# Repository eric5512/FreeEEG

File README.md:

# FreeEEG

FreeEEG is a low-cost, open-source electroencephalography (EEG) acquisition platform designed for educational, experimental, and research-oriented applications. The project aims to provide an accessible and modifiable EEG system for researchers, students, and hobbyists who need direct control over the acquisition hardware, firmware, and data interface.

The platform is based on the **Texas Instruments ADS1299** analog front-end and an **ESP32-S3** microcontroller. It supports multichannel EEG acquisition, real-time wireless data transmission, onboard storage, and motion sensing through an integrated IMU.

> **Safety notice:** FreeEEG is not a medical device. It has not been medically certified and must not be used for clinical diagnosis, treatment, or any safety-critical medical application.

## Project Overview

The system was developed as a Master Thesis project at the Institut d'Investigacions Biomèdiques August Pi i Sunyer (IDIBAPS). The main objective is to create an open-source and open-hardware EEG platform that is cost-effective, configurable, and easy to adapt to different experimental scenarios.

The current prototype integrates:

- 8-channel EEG acquisition
- ADS1299 24-bit analog front-end
- ESP32-S3 microcontroller
- WiFi access point mode
- UDP real-time data streaming
- HTTP-based configuration interface
- SD card storage through SDIO
- ICM42670 accelerometer and gyroscope
- ICS43434 microphone
- QWIIC connector for I2C external peripherals
- Battery-powered operation
- Python client library for receiving and decoding data

## Repository Structure

```text
FreeEEG/
├── Client/
│   └── Python library and tools for interacting with the device
│
├── Electronics/
│   └── KiCad schematic, PCB layout, and manufacturing files
│
├── Firmware/
│   └── ESP32-S3 firmware based on ESP-IDF and FreeRTOS
│
└── README.md
```

## Hardware Architecture

The hardware is centered around the ADS1299, an 8-channel, 24-bit analog front-end designed for EEG and biopotential measurements. The ESP32-S3 handles acquisition control, wireless communication, SD card storage, configuration, and system management.

Main hardware components:

| Subsystem | Component |
|---|---|
| Analog front-end | ADS1299 |
| Microcontroller | ESP32-S3 |
| IMU | ICM42670 |
| Microphone | ICS43434 |
| Storage | microSD card |
| Wireless communication | ESP32-S3 WiFi |
| Configuration interface | HTTP server |
| Real-time streaming | UDP |
| PCB design tool | KiCad |

> **Warning:** The PCB still presents some issues in its current form. More modifications need to be introduced to release the first fully functional version

## Firmware

The firmware is developed using **ESP-IDF** and **FreeRTOS**. It is organized into concurrent tasks to separate time-critical acquisition from communication, storage, and configuration logic.

Main firmware functions:

- ADS1299 initialization and register configuration
- EEG acquisition synchronized with the ADS1299 `DRDY` signal
- IMU acquisition over I2C
- UDP packet transmission in online mode
- CSV data logging to SD card in offline mode
- HTTP configuration server
- Mode selection through a physical switch

The firmware supports two operating modes:

### Online Mode

In online mode, the ESP32-S3 creates a WiFi access point and waits for UDP commands from the client. EEG and IMU data are transmitted in real time using UDP packets.

### Offline Mode

In offline mode, acquisition starts automatically and data are stored locally on the SD card in CSV format. WiFi is disabled to reduce power consumption.

## Client Library

The `Client/` folder contains the Python interface used to communicate with the device. The client library provides a higher-level interface for:

- Connecting to the FreeEEG device
- Sending start and stop commands
- Receiving UDP data packets
- Decoding EEG, IMU, and event data
- Exporting samples to CSV
- Building custom visualization or processing tools

Basic usage example:

```python
from freeeeg import FreeEEG
import signal

if __name__ == "__main__":
    eeg = FreeEEG()

    def signal_handler(sig, frame):
        f.close()
        eeg.stop()
        print("Stopping measurements")
        exit(0)

    signal.signal(signal.SIGINT, signal_handler)

    data_stream = eeg.get_data_generator(blocking=True)

    f = open("test.csv", "w+")
    eeg.start()

    print("Starting EEG...")
    f.write("timestamp,e1,e2,e3,e4,e5,e6,e7,e8,ax,ay,az,gx,gy,gz,event\n")

    for sample in data_stream():
        f.write(sample.as_csv() + "\n")
```

## Electronics

The `Electronics/` folder contains the KiCad project files needed to inspect, modify, and manufacture the PCB.

This folder may include:

- KiCad schematic files
- KiCad PCB layout files
- Symbol and footprint libraries
- Gerber files
- Drill files
- Bill of materials
- Assembly files

The current PCB revision is an engineering prototype. Before manufacturing or using the board, review the schematic, layout, footprints, and known issues.

## Current Prototype Status

The current version should be considered a functional engineering prototype. Several subsystems have been validated, including ADS1299 communication, EEG acquisition using the evaluation platform, WiFi access point creation, UDP transmission, HTTP configuration, and Python packet decoding.

Preliminary validation demonstrated:

- EEG acquisition with dry electrodes
- Resting-state EEG activity with a visible alpha-band peak around 10 Hz
- Shorted-input RMS noise around 0.2 µV RMS
- Stable UDP transmission at approximately 100 packets/s
- Packet loss at higher packet rates around 250 packets/s
- Approximate current consumption of 110 mA in online mode and 60 mA in offline mode
- Indoor wireless range around 10 m

## Known Limitations

The current prototype has several limitations:

- Not medically certified
- Not intended for clinical or diagnostic use
- Firmware validation still ongoing
- No integrated electrode impedance measurement
- No dedicated external synchronization connector in the current revision
- Long-duration validation is still required

## Planned Improvements

Future development may include:

- Complete firmware validation
- Full integration testing
- Electrode impedance measurement
- Improved analog filtering
- Bluetooth or mobile interface support
- Real-time visualization tools
- Signal processing and neurofeedback utilities

## Development Requirements

### Firmware

Recommended tools:

- ESP-IDF
- FreeRTOS
- ESP32-S3 toolchain
- Python tools for flashing and monitoring

### Electronics

Recommended tools:

- KiCad
- Gerber viewer

### Client

Recommended tools:

- Python 3
- NumPy
- Matplotlib
- Standard socket library

Exact Python dependencies should be listed in a future `requirements.txt`.

## Contributing

Contributions are welcome, especially in the following areas:

- Firmware validation
- Python client improvements
- Real-time plotting tools
- PCB review
- Documentation
- Signal processing examples
- Neurofeedback experiments
- Long-duration acquisition testing

When contributing hardware changes, document the PCB revision clearly and include updated manufacturing files.

## Disclaimer

This project is provided for educational, research, and experimental use only. It is not designed, certified, or validated as a medical device. Use only battery-powered operation during human measurements, and follow appropriate electrical safety practices.

The authors and contributors are not responsible for misuse of the hardware, firmware, or software.

## TODO list:
- [ ] Add biofeedback example scripts.
- [ ] Add bluetooth mode along with Android app.

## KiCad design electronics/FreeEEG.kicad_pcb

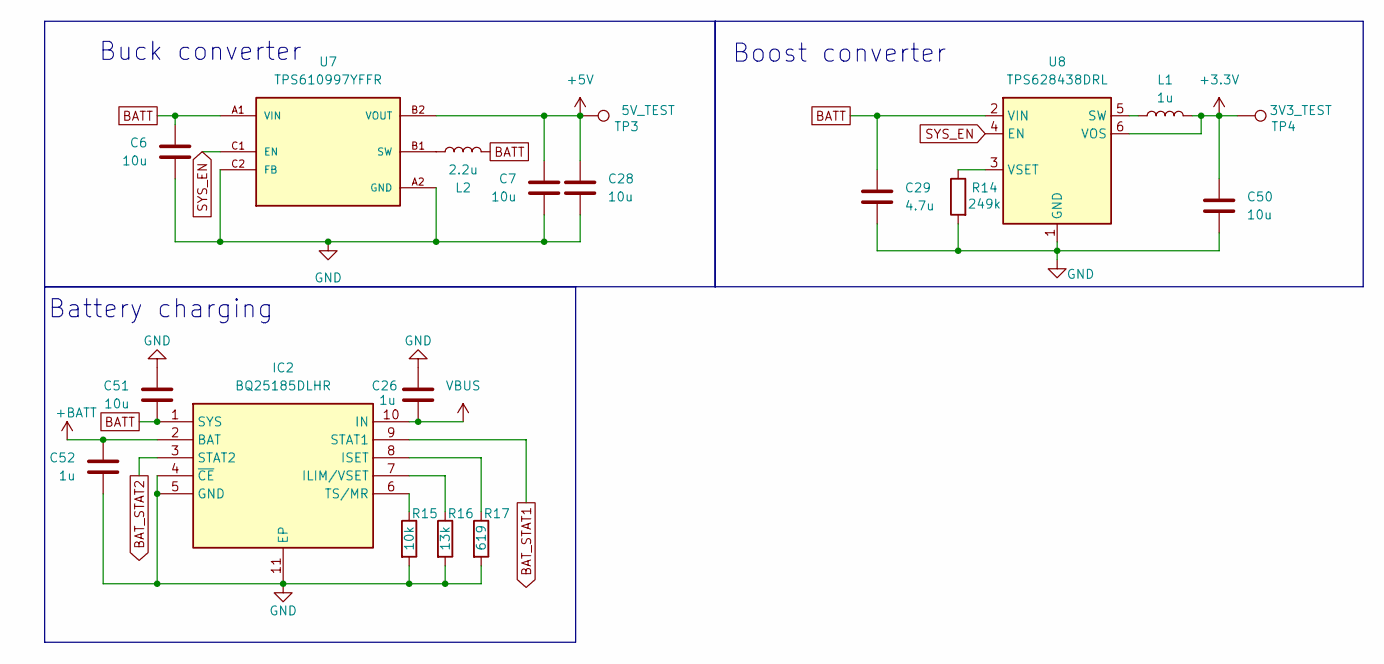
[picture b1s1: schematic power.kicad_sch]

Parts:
C6, C7, C28, C50, C51: 10u; C_0402_1005Metric
C26, C52: 1u; C_0402_1005Metric
C29: 4.7u; C_0402_1005Metric
IC2: BQ25185DLHR; SON40P220X200X80-11N; Manufacturer_Part_Number BQ25185DLHR; Mouser Part Number 595-BQ25185DLHR
L1: 1u; L_1008_2520Metric
L2: 2.2u; PIS2D18LP
R14: 249k; R_0603_1608Metric
R15: 10k; R_0603_1608Metric
R16: 13k; R_0603_1608Metric
R17: 619; R_0603_1608Metric
TP3: 5V_TEST; TestPoint_Pad_D1.5mm
TP4: 3V3_TEST; TestPoint_Pad_D1.5mm
U7: TPS610997YFFR; BGA6N40P3X2_122X88X62N; PARTREV K
U8: TPS628438DRL; SOT-563

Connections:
+3.3V: C50.1, L1.2, TP4.1 (1_1), U8.6 (VOS); also elsewhere on the board
+5V: C7.1, C28.1, TP3.1 (1_1), U7.B2 (VOUT); also elsewhere on the board
+BATT: C52.1, IC2.2 (BAT); also elsewhere on the board
BATT: C6.1, C29.1, C51.2, IC2.1 (SYS), L2.1, U7.A1 (VIN), U8.2 (VIN); also elsewhere on the board
BAT_STAT1: IC2.9 (STAT1); also elsewhere on the board
BAT_STAT2: IC2.3 (STAT2); also elsewhere on the board
GND: C6.2, C7.2, C26.1, C28.2, C29.2, C50.2, C51.1, C52.2, IC2.4 (~CE), IC2.5 (GND), IC2.11 (EP), R14.2, R15.2, R16.2, R17.2, U7.A2 (GND), U7.C2 (FB), U8.1 (GND); also elsewhere on the board
unnamed: IC2.7 (ILIM/VSET), R16.1
unnamed: IC2.8 (ISET), R17.1
unnamed: IC2.6 (TS/MR), R15.1
unnamed: L2.2, U7.B1 (SW)
unnamed: L1.1, U8.5 (SW)
unnamed: R14.1, U8.3 (VSET)
SYS_EN: U7.C1 (EN), U8.4 (EN); also elsewhere on the board
VBUS: C26.2, IC2.10 (IN); also elsewhere on the board

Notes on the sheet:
Battery charging
Buck converter
Boost converter

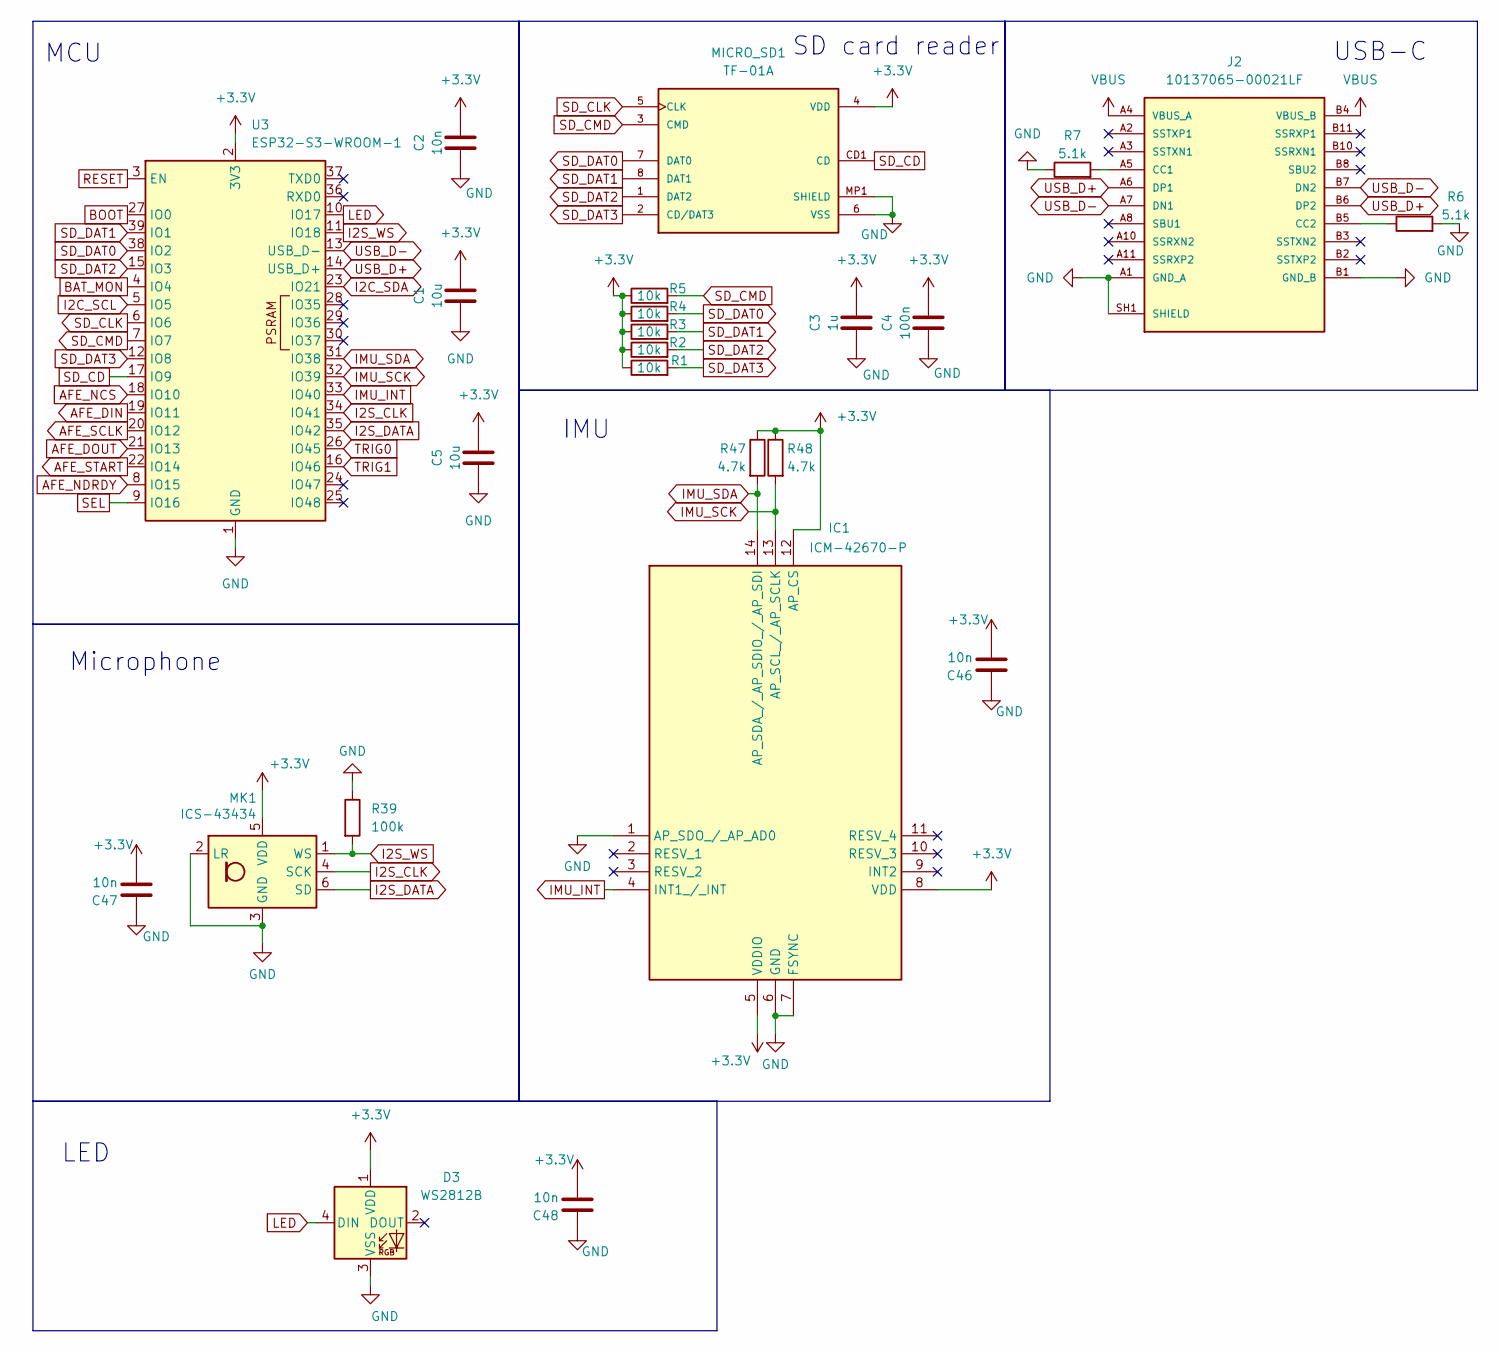
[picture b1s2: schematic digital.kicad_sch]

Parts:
C1, C5: 10u; C_0805_2012Metric
C2: 10n; C_0805_2012Metric
C3: 1u; C_0805_2012Metric
C4: 100n; C_0805_2012Metric
C46, C47, C48: 10n; C_0603_1608Metric
D3: WS2812B; LED_WS2812B_PLCC4_5.0x5.0mm_P3.2mm
IC1: ICM-42670-P; ICM42670P; Manufacturer_Part_Number ICM-42670-P; Mouser Part Number 410-ICM-42670-P
J2: 10137065-00021LF; AMPHENOL_10137065-00021LF; PARTREV D
MICRO_SD1: TF-01A
MK1: ICS-43434; ICS43434
R1, R2, R3, R4, R5: 10k; R_0603_1608Metric
R6, R7: 5.1k; R_0603_1608Metric
R39: 100k; R_0603_1608Metric
R47, R48: 4.7k; R_0603_1608Metric
U3: ESP32-S3-WROOM-1

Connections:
+3.3V: C1.2, C2.1, C3.2, C4.1, C5.2, C46.2, C47.2, C48.2, D3.1 (VDD), IC1.5 (VDDIO), IC1.8 (VDD), IC1.12 (AP_CS), MICRO_SD1.4 (VDD), MK1.5 (VDD), R1.1, R2.1, R3.1, R4.1, R5.1, R47.1, R48.1, U3.2 (3V3); also elsewhere on the board
AFE_DIN: U3.19 (IO11); also elsewhere on the board
AFE_DOUT: U3.21 (IO13); also elsewhere on the board
AFE_NCS: U3.18 (IO10); also elsewhere on the board
AFE_NDRDY: U3.8 (IO15); also elsewhere on the board
AFE_SCLK: U3.20 (IO12); also elsewhere on the board
AFE_START: U3.22 (IO14); also elsewhere on the board
BAT_MON: U3.4 (IO4); also elsewhere on the board
BOOT: U3.27 (IO0); also elsewhere on the board
GND: C1.1, C2.2, C3.1, C4.2, C5.1, C46.1, C47.1, C48.1, D3.3 (VSS), IC1.1 (AP_SDO_/_AP_AD0), IC1.6 (GND), IC1.7 (FSYNC), J2.A1 (GND_A), J2.A12 (GND_A), J2.B1 (GND_B), J2.B12 (GND_B), J2.SH1 (SHIELD), J2.SH2 (SHIELD), J2.SH3 (SHIELD), J2.SH4 (SHIELD), MICRO_SD1.6 (VSS), MICRO_SD1.MP1 (SHIELD), MICRO_SD1.MP2 (SHIELD), MICRO_SD1.MP3 (SHIELD), MICRO_SD1.MP4 (SHIELD), MK1.2 (LR), MK1.3 (GND), R6.2, R7.1, R39.1, U3.1 (GND), U3.40 (GND), U3.41 (GND); also elsewhere on the board
I2C_SCL: U3.5 (IO5); also elsewhere on the board
I2C_SDA: U3.23 (IO21); also elsewhere on the board
I2S_CLK: MK1.4 (SCK), U3.34 (IO41)
I2S_DATA: MK1.6 (SD), U3.35 (IO42)
I2S_WS: MK1.1 (WS), R39.2, U3.11 (IO18)
IMU_INT: IC1.4 (INT1_/_INT), U3.33 (IO40)
IMU_SCK: IC1.13 (AP_SCL_/_AP_SCLK), R48.2, U3.32 (IO39)
IMU_SDA: IC1.14 (AP_SDA_/_AP_SDIO_/_AP_SDI), R47.2, U3.31 (IO38)
LED: D3.4 (DIN), U3.10 (IO17)
unnamed: J2.A5 (CC1), R7.2
unnamed: J2.B5 (CC2), R6.1
RESET: U3.3 (EN); also elsewhere on the board
SD_CD: MICRO_SD1.CD1 (CD), U3.17 (IO9)
SD_CLK: MICRO_SD1.5 (CLK), U3.6 (IO6)
SD_CMD: MICRO_SD1.3 (CMD), R5.2, U3.7 (IO7)
SD_DAT0: MICRO_SD1.7 (DAT0), R4.2, U3.38 (IO2)
SD_DAT1: MICRO_SD1.8 (DAT1), R3.2, U3.39 (IO1)
SD_DAT2: MICRO_SD1.1 (DAT2), R2.2, U3.15 (IO3)
SD_DAT3: MICRO_SD1.2 (CD/DAT3), R1.2, U3.12 (IO8)
SEL: U3.9 (IO16); also elsewhere on the board
TRIG0: U3.26 (IO45); also elsewhere on the board
TRIG1: U3.16 (IO46); also elsewhere on the board
USB_D+: J2.A6 (DP1), J2.B6 (DP2), U3.14 (USB_D+)
USB_D-: J2.A7 (DN1), J2.B7 (DN2), U3.13 (USB_D-)
VBUS: J2.A4 (VBUS_A), J2.A9 (VBUS_A), J2.B4 (VBUS_B), J2.B9 (VBUS_B); also elsewhere on the board

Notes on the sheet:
MCU
IMU
SD card reader
Microphone
LED
USB-C

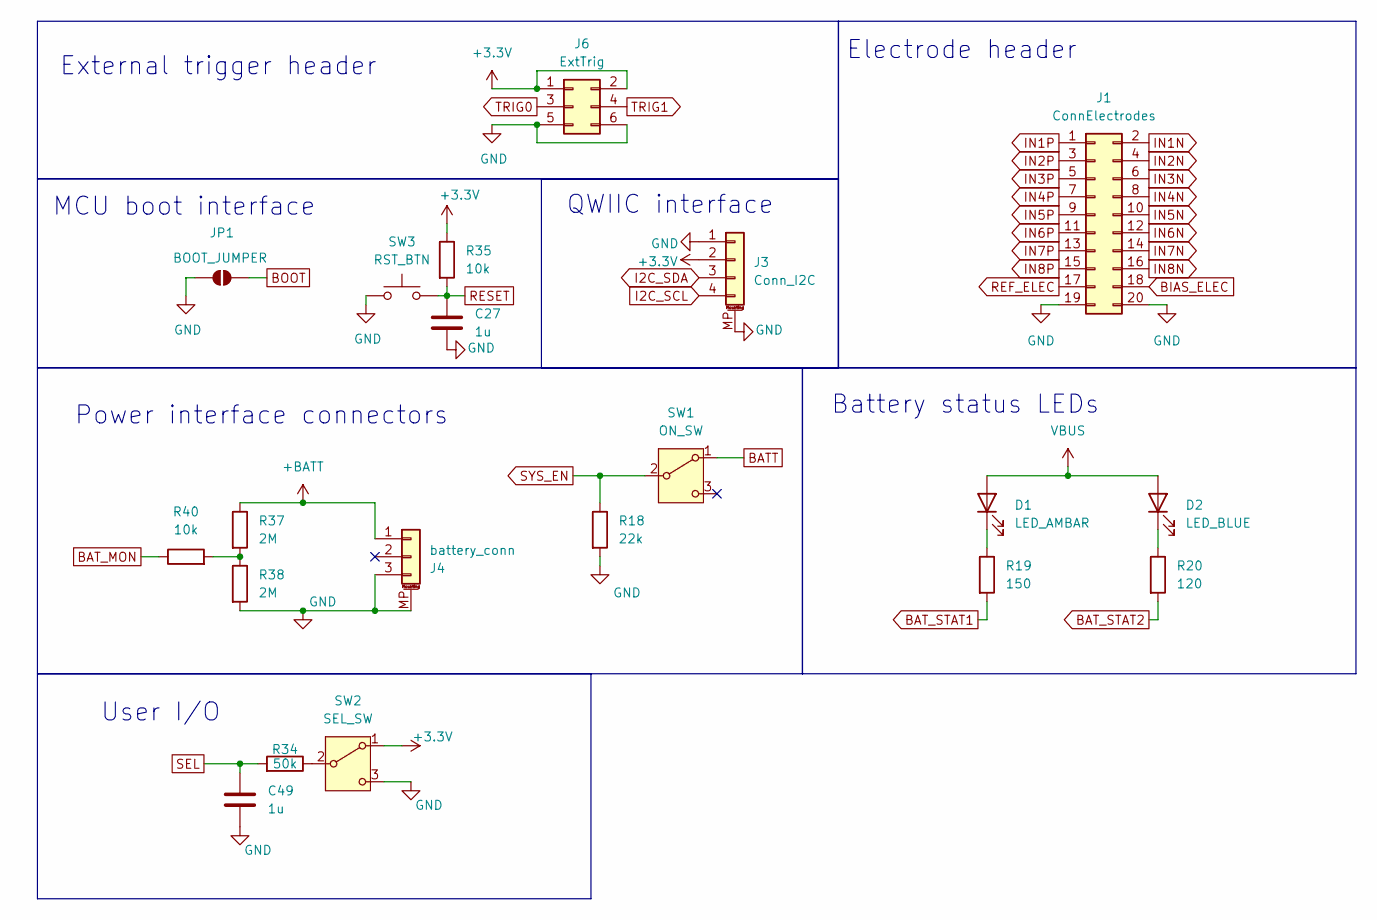
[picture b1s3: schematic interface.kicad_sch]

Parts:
C27: 1u; C_0805_2012Metric
C49: 1u; C_0603_1608Metric
D1: LED_AMBAR; LED_0603_1608Metric
D2: LED_BLUE; LED_0603_1608Metric
J1: ConnElectrodes; PinHeader_2x10_P2.54mm_Vertical
J3: Conn_I2C; JST_SH_SM04B-SRSS-TB_1x04-1MP_P1.00mm_Horizontal
J4: battery_conn; Molex_PicoBlade_53261-0371_1x03-1MP_P1.25mm_Horizontal
J6: ExtTrig; PinHeader_2x03_P2.54mm_Vertical_SMD; JLCPCB C192301
JP1: BOOT_JUMPER; SolderJumper-2_P1.3mm_Open_Pad1.0x1.5mm
R18: 22k; R_0603_1608Metric
R19: 150; R_0603_1608Metric
R20: 120; R_0603_1608Metric
R34: 50k; R_0603_1608Metric
R35, R40: 10k; R_0603_1608Metric
R37, R38: 2M; R_0603_1608Metric
SW1: ON_SW; K3-1260D-L1
SW2: SEL_SW; K3-1260D-L1
SW3: RST_BTN; K2-1187SQ-A4SW-06

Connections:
+3.3V: J3.2, J6.1, J6.2, R35.1, SW2.1 (A); also elsewhere on the board
+BATT: J4.1, R37.1; also elsewhere on the board
BATT: SW1.1 (A); also elsewhere on the board
BAT_MON: R40.1; also elsewhere on the board
BAT_STAT1: R19.2; also elsewhere on the board
BAT_STAT2: R20.2; also elsewhere on the board
BIAS_ELEC: J1.18; also elsewhere on the board
BOOT: JP1.2 (B); also elsewhere on the board
GND: C27.2, C49.2, J1.19, J1.20, J3.1, J3.MP (MountPin), J4.3, J4.MP (MountPin), J6.5, J6.6, JP1.1 (A), R18.2, R38.2, SW2.3 (C), SW3.1; also elsewhere on the board
I2C_SCL: J3.4; also elsewhere on the board
I2C_SDA: J3.3; also elsewhere on the board
IN1N: J1.2; also elsewhere on the board
IN1P: J1.1; also elsewhere on the board
IN2N: J1.4; also elsewhere on the board
IN2P: J1.3; also elsewhere on the board
IN3N: J1.6; also elsewhere on the board
IN3P: J1.5; also elsewhere on the board
IN4N: J1.8; also elsewhere on the board
IN4P: J1.7; also elsewhere on the board
IN5N: J1.10; also elsewhere on the board
IN5P: J1.9; also elsewhere on the board
IN6N: J1.12; also elsewhere on the board
IN6P: J1.11; also elsewhere on the board
IN7N: J1.14; also elsewhere on the board
IN7P: J1.13; also elsewhere on the board
IN8N: J1.16; also elsewhere on the board
IN8P: J1.15; also elsewhere on the board
unnamed: D1.1 (K), R19.1
unnamed: D2.1 (K), R20.1
unnamed: R37.2, R38.1, R40.2
unnamed: R34.1, SW2.2 (B)
REF_ELEC: J1.17; also elsewhere on the board
RESET: C27.1, R35.2, SW3.2; also elsewhere on the board
SEL: C49.1, R34.2; also elsewhere on the board
SYS_EN: R18.1, SW1.2 (B); also elsewhere on the board
TRIG0: J6.3; also elsewhere on the board
TRIG1: J6.4; also elsewhere on the board
VBUS: D1.2 (A), D2.2 (A); also elsewhere on the board

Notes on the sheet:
MCU boot interface
User I/O
QWIIC interface
Battery status LEDs
External trigger header
Power interface connectors
Electrode header

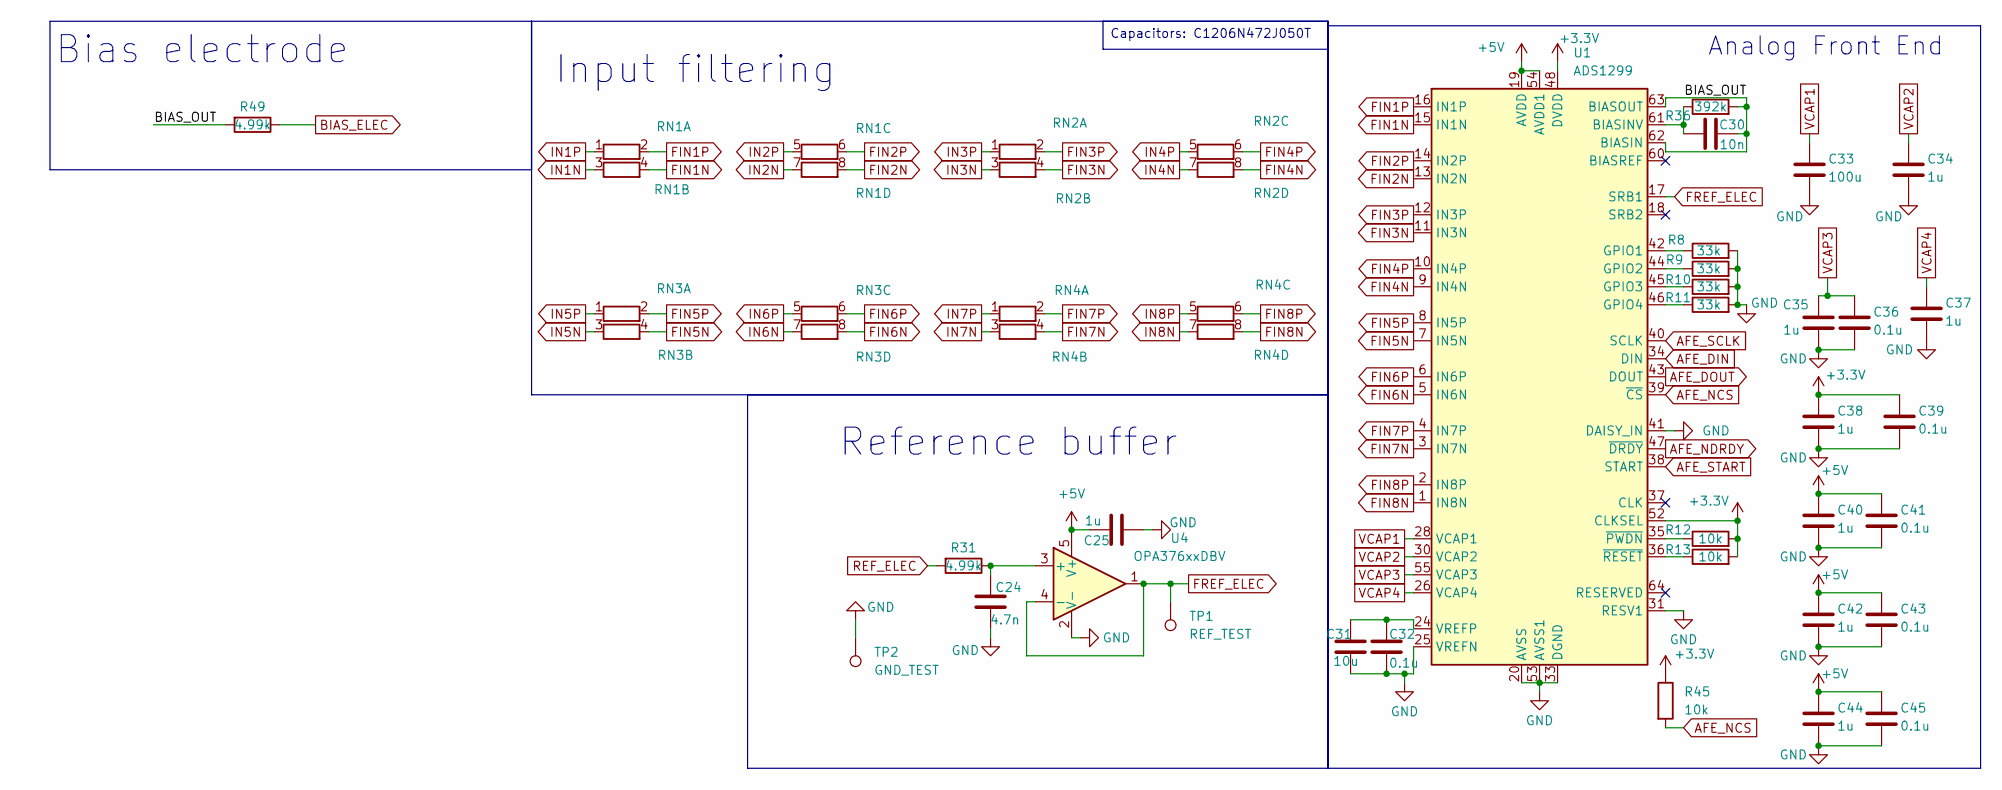
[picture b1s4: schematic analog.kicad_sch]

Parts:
C24: 4.7n; C_0603_1608Metric
C25: 1u; C_0805_2012Metric
C30: 10n; C_0603_1608Metric
C31: 10u; C_0805_2012Metric
C32, C36, C39, C41, C43, C45: 0.1u; C_0603_1608Metric
C33: 100u; C_1206_3216Metric
C34, C35, C37, C38, C40, C42, C44: 1u; C_0603_1608Metric
R8, R9, R10, R11: 33k; R_0603_1608Metric
R12, R13, R45: 10k; R_0603_1608Metric
R31, R49: 4.99k; R_0603_1608Metric
R36: 392k; R_0603_1608Metric
RN1, RN2, RN3, RN4: R_Pack04_SIP_Split; 4D03WGF5101T5E
TP1: REF_TEST; TestPoint_Pad_D1.5mm
TP2: GND_TEST; TestPoint_Pad_D1.5mm
U1: ADS1299; TQFP-64_10x10mm_P0.5mm
U4: OPA376xxDBV; SOT-23-5

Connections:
+3.3V: C38.1, C39.1, R12.2, R13.2, R45.1, U1.48 (DVDD), U1.50 (DVDD), U1.52 (CLKSEL); also elsewhere on the board
+5V: C25.2, C40.1, C41.1, C42.1, C43.1, C44.1, C45.1, U1.19 (AVDD), U1.21 (AVDD), U1.22 (AVDD), U1.54 (AVDD1), U1.56 (AVDD), U1.59 (AVDD), U4.5 (V+); also elsewhere on the board
/Analog/BIAS_OUT: C30.2, R36.2, R49.2, U1.62 (BIASIN), U1.63 (BIASOUT)
AFE_DIN: U1.34 (DIN); also elsewhere on the board
AFE_DOUT: U1.43 (DOUT); also elsewhere on the board
AFE_NCS: R45.2, U1.39 (~CS); also elsewhere on the board
AFE_NDRDY: U1.47 (~DRDY); also elsewhere on the board
AFE_SCLK: U1.40 (SCLK); also elsewhere on the board
AFE_START: U1.38 (START); also elsewhere on the board
BIAS_ELEC: R49.1; also elsewhere on the board
FIN1N: RN1.4 (R2.2), U1.15 (IN1N)
FIN1P: RN1.2 (R1.2), U1.16 (IN1P)
FIN2N: RN1.8 (R4.2), U1.13 (IN2N)
FIN2P: RN1.6 (R3.2), U1.14 (IN2P)
FIN3N: RN2.4 (R2.2), U1.11 (IN3N)
FIN3P: RN2.2 (R1.2), U1.12 (IN3P)
FIN4N: RN2.8 (R4.2), U1.9 (IN4N)
FIN4P: RN2.6 (R3.2), U1.10 (IN4P)
FIN5N: RN3.4 (R2.2), U1.7 (IN5N)
FIN5P: RN3.2 (R1.2), U1.8 (IN5P)
FIN6N: RN3.8 (R4.2), U1.5 (IN6N)
FIN6P: RN3.6 (R3.2), U1.6 (IN6P)
FIN7N: RN4.4 (R2.2), U1.3 (IN7N)
FIN7P: RN4.2 (R1.2), U1.4 (IN7P)
FIN8N: RN4.8 (R4.2), U1.1 (IN8N)
FIN8P: RN4.6 (R3.2), U1.2 (IN8P)
FREF_ELEC: TP1.1 (1_1), U1.17 (SRB1), U4.1, U4.4 (-)
GND: C24.2, C25.1, C31.2, C32.2, C33.2, C34.2, C35.2, C36.2, C37.2, C38.2, C39.2, C40.2, C41.2, C42.2, C43.2, C44.2, C45.2, R8.2, R9.2, R10.2, R11.2, TP2.1 (1_1), U1.20 (AVSS), U1.23 (AVSS), U1.25 (VREFN), U1.31 (RESV1), U1.32 (AVSS), U1.33 (DGND), U1.41 (DAISY_IN), U1.49 (DGND), U1.51 (DGND), U1.53 (AVSS1), U1.57 (AVSS), U1.58 (AVSS), U4.2 (V-); also elsewhere on the board
IN1N: RN1.3 (R2.1); also elsewhere on the board
IN1P: RN1.1 (R1.1); also elsewhere on the board
IN2N: RN1.7 (R4.1); also elsewhere on the board
IN2P: RN1.5 (R3.1); also elsewhere on the board
IN3N: RN2.3 (R2.1); also elsewhere on the board
IN3P: RN2.1 (R1.1); also elsewhere on the board
IN4N: RN2.7 (R4.1); also elsewhere on the board
IN4P: RN2.5 (R3.1); also elsewhere on the board
IN5N: RN3.3 (R2.1); also elsewhere on the board
IN5P: RN3.1 (R1.1); also elsewhere on the board
IN6N: RN3.7 (R4.1); also elsewhere on the board
IN6P: RN3.5 (R3.1); also elsewhere on the board
IN7N: RN4.3 (R2.1); also elsewhere on the board
IN7P: RN4.1 (R1.1); also elsewhere on the board
IN8N: RN4.7 (R4.1); also elsewhere on the board
IN8P: RN4.5 (R3.1); also elsewhere on the board
unnamed: C30.1, R36.1, U1.61 (BIASINV)
unnamed: R8.1, U1.42 (GPIO1)
unnamed: R9.1, U1.44 (GPIO2)
unnamed: R10.1, U1.45 (GPIO3)
unnamed: R11.1, U1.46 (GPIO4)
unnamed: C31.1, C32.1, U1.24 (VREFP)
unnamed: R12.1, U1.35 (~PWDN)
unnamed: R13.1, U1.36 (~RESET)
unnamed: C24.1, R31.1, U4.3 (+)
REF_ELEC: R31.2; also elsewhere on the board
VCAP1: C33.1, U1.28 (VCAP1)
VCAP2: C34.1, U1.30 (VCAP2)
VCAP3: C35.1, C36.1, U1.55 (VCAP3)
VCAP4: C37.1, U1.26 (VCAP4)

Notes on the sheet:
Reference buffer
Input filtering
Analog Front End
Bias electrode
Capacitors: C1206N472J050T

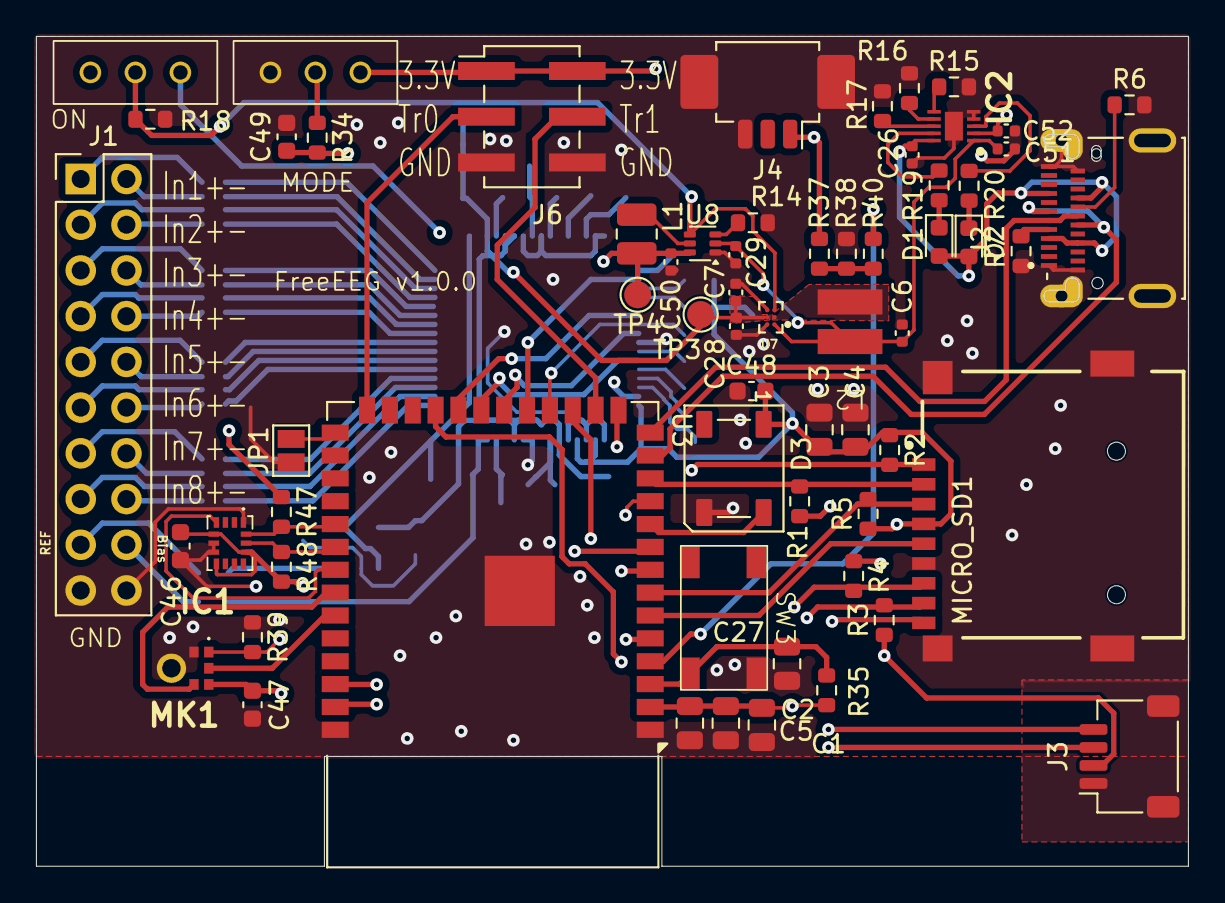
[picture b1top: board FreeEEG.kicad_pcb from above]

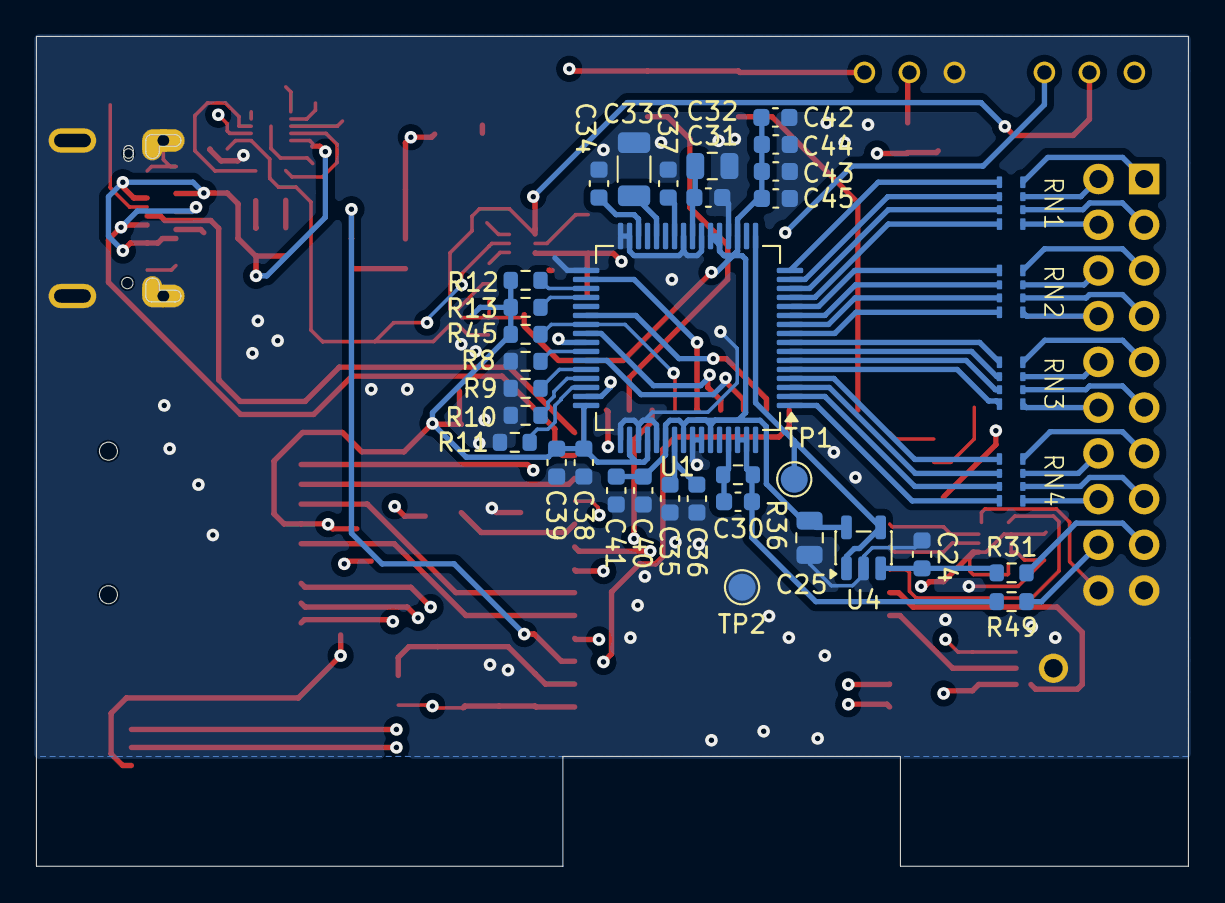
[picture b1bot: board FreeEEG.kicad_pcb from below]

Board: 4 copper layers, 64.0 x 46.1 mm, 99 parts (36 on the bottom side), 100 nets.

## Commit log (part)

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2025-09-11 Working on front end
    Started developing:
    - ESP8266 web server and UDP data transmission
    - Python library for data reception + Matplotlib animation
2025-11-10 Preparing for fork
2026-03-18 Changing packet organization
2026-05-08 Starting final firmware development
2026-05-11 Added driver for ADS1299 and added wifi app files
2026-05-23 Preparing demo
2026-05-23 Changing .gitignore
2026-06-01 Identified timing issues
2026-06-02 Solving the timing issues in the firmware and adding a decent README.md
2026-06-04 Changing README.md
2026-06-05 Using proper python module structure
2026-06-05 Adding more examples and removing useless files
2026-06-21 Working on real time plotting
